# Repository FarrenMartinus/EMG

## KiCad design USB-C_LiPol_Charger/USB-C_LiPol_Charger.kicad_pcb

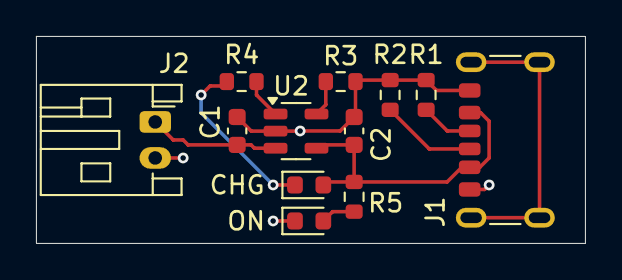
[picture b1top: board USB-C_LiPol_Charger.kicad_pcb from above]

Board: 2 copper layers, 30.5 x 11.5 mm, 12 parts (0 on the bottom side), 9 nets.

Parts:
C1, C2: 4.7u; C_0603_1608Metric
CHG: LED; LED_0603_1608Metric
J1: USB-C Port; USB_C_Receptacle_GCT_USB4125-xx-x_6P_TopMnt_Horizontal
J2: Conn_01x02; JST_PH_S2B-PH-K_1x02_P2.00mm_Horizontal
ON: LED; LED_0603_1608Metric
R1, R2: 5.1k; R_0603_1608Metric
R3: 2k; R_0603_1608Metric
R4, R5: 470; R_0603_1608Metric
U2: MCP73831; SOT-23-5

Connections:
GND: C1.2, C2.2, J1.A12 (GND), J1.B12 (GND), J2.2, ON.1 (K), R1.2, R2.2, R3.2, U2.2 (V_{SS})
unnamed: C2.1, CHG.2 (A), J1.A9 (VBUS), J1.B9 (VBUS), R5.1, U2.4 (V_{DD})
unnamed: CHG.1 (K), R4.1
unnamed: ON.2 (A), R5.2
unnamed: J1.A5 (CC1), R2.1
unnamed: J1.B5 (CC2), R1.1
unnamed: C1.1, J2.1, U2.3 (V_{BAT})
unnamed: R3.1, U2.5 (PROG)
unnamed: R4.2, U2.1 (STAT)

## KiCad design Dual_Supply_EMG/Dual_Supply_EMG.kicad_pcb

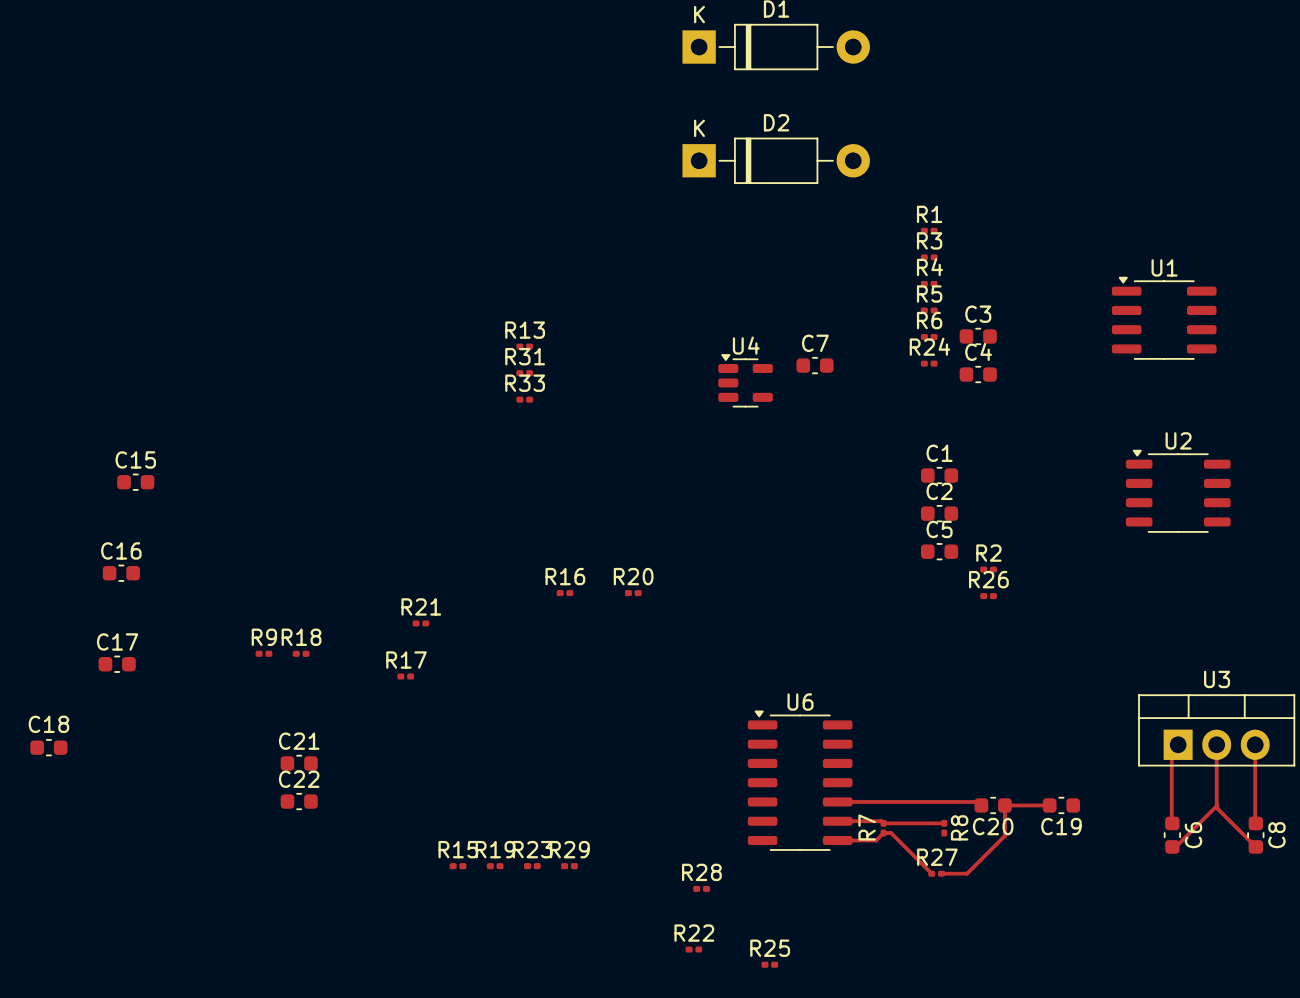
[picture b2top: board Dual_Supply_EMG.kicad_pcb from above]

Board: 2 copper layers, 50 parts (0 on the bottom side), 32 nets.

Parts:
C1: .1u; C_0603_1608Metric
C2: 10u; C_0603_1608Metric
C3, C4: .22u; C_0603_1608Metric
C5: 10n; C_0603_1608Metric
C6: 0.33u; C_0603_1608Metric
C7: 47n; C_0603_1608Metric
C8: 0.1u; C_0603_1608Metric
C15, C16, C17, C18: 33n; C_0603_1608Metric
C19, C20, C21, C22: 0.82u; C_0603_1608Metric
D1: 1N47xxA; D_DO-41_SOD81_P10.16mm_Horizontal
D2: 1N5819; D_DO-41_SOD81_P10.16mm_Horizontal
R1, R3: 82k; R_0201_0603Metric
R2: 2k; R_0201_0603Metric
R4, R5, R9, R18: 12k; R_0201_0603Metric
R6, R24: 100k; R_0201_0603Metric
R7, R16: 1.5k; R_0201_0603Metric
R8, R15, R17, R19, R20, R21, R22, R23, R25, R27, R28, R29: 10k; R_0201_0603Metric
R13: 680k; R_0201_0603Metric
R26: 1M; R_0201_0603Metric
R31: 330k; R_0201_0603Metric
R33: 1k; R_0201_0603Metric
U1: TL072; SOIC-8_3.9x4.9mm_P1.27mm
U2: INA128; SO-8_3.9x4.9mm_P1.27mm
U3: LM7806_TO220; TO-220-3_Vertical
U4: MCP6021; TSOT-23-5
U6: TL074; SOIC-14_3.9x8.7mm_P1.27mm

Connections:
0: C1.1, C2.2, C6.2, C8.2, C15.1, C17.2, D2.2 (A), R31.1, U1.4 (V-), U2.4 (V-), U3.2 (GND), U4.4 (V-), U6.11 (V-)
+6V: C8.1, R3.2, R8.2, R13.1, R15.2, R17.2, R19.2, R25.2, R26.2, R28.2, U2.2 (-), U2.6 (Ref), U3.3 (VO), U4.3 (V+)
+12V: C1.2, C2.1, C6.1, U1.8 (V+), U2.3 (V+), U3.1 (VI), U6.4 (V+)
/60Hz_Notch_Filter/NOTCH_IN: C3.1, C18.2, R1.2, R18.1, R24.2, U6.7
/60Hz_Notch_Filter/NOTCH_OUT: C7.2, R4.1, R6.1, U1.1
/EMG_Band_Pass_Filter/BP_IN: C19.1, U2.5
unnamed: C4.1, R5.2, U1.7
unnamed: C16.1, R20.2, R21.1
unnamed: C16.2, R16.1, R22.1, U6.1
unnamed: C18.1, R22.2, R23.1
unnamed: C19.2, C20.1, R27.2
unnamed: C21.1, R7.1, R27.1, U6.8
unnamed: C21.2, C22.1, R29.1
unnamed: D1.1 (K), R33.2
unnamed: R2.1, U2.8 (Rg)
unnamed: R2.2, U2.7 (Rg)
unnamed: R9.1, R20.1, R29.2, U6.14
unnamed: C3.2, R1.1, R3.1, R5.1, U1.3 (+)
unnamed: C4.2, R4.2, U1.2 (-), U1.6 (-)
unnamed: R6.2, R24.1, U1.5 (+)
unnamed: C5.2, R26.1, U2.1 (+)
unnamed: C7.1, R13.2, R31.2, U4.1 (+)
unnamed: R33.1, U4.2 (-), U4.5
unnamed: C15.2, R21.2, U6.3 (+)
unnamed: R16.2, R17.1, U6.2 (-)
unnamed: C17.1, R23.2, U6.5 (+)
unnamed: R18.2, R19.1, U6.6 (-)
unnamed: C20.2, R25.1, U6.10 (+)
unnamed: R7.2, R8.1, U6.9 (-)
unnamed: C22.2, R28.1, U6.12 (+)
unnamed: R9.2, R15.1, U6.13 (-)
OUTPUT: D1.2 (A), D2.1 (K)

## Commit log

2025-05-30 Initial commit: All EMG Iterations
2025-06-01 USB-C LiPo Charger
2025-06-01 misc. changes
